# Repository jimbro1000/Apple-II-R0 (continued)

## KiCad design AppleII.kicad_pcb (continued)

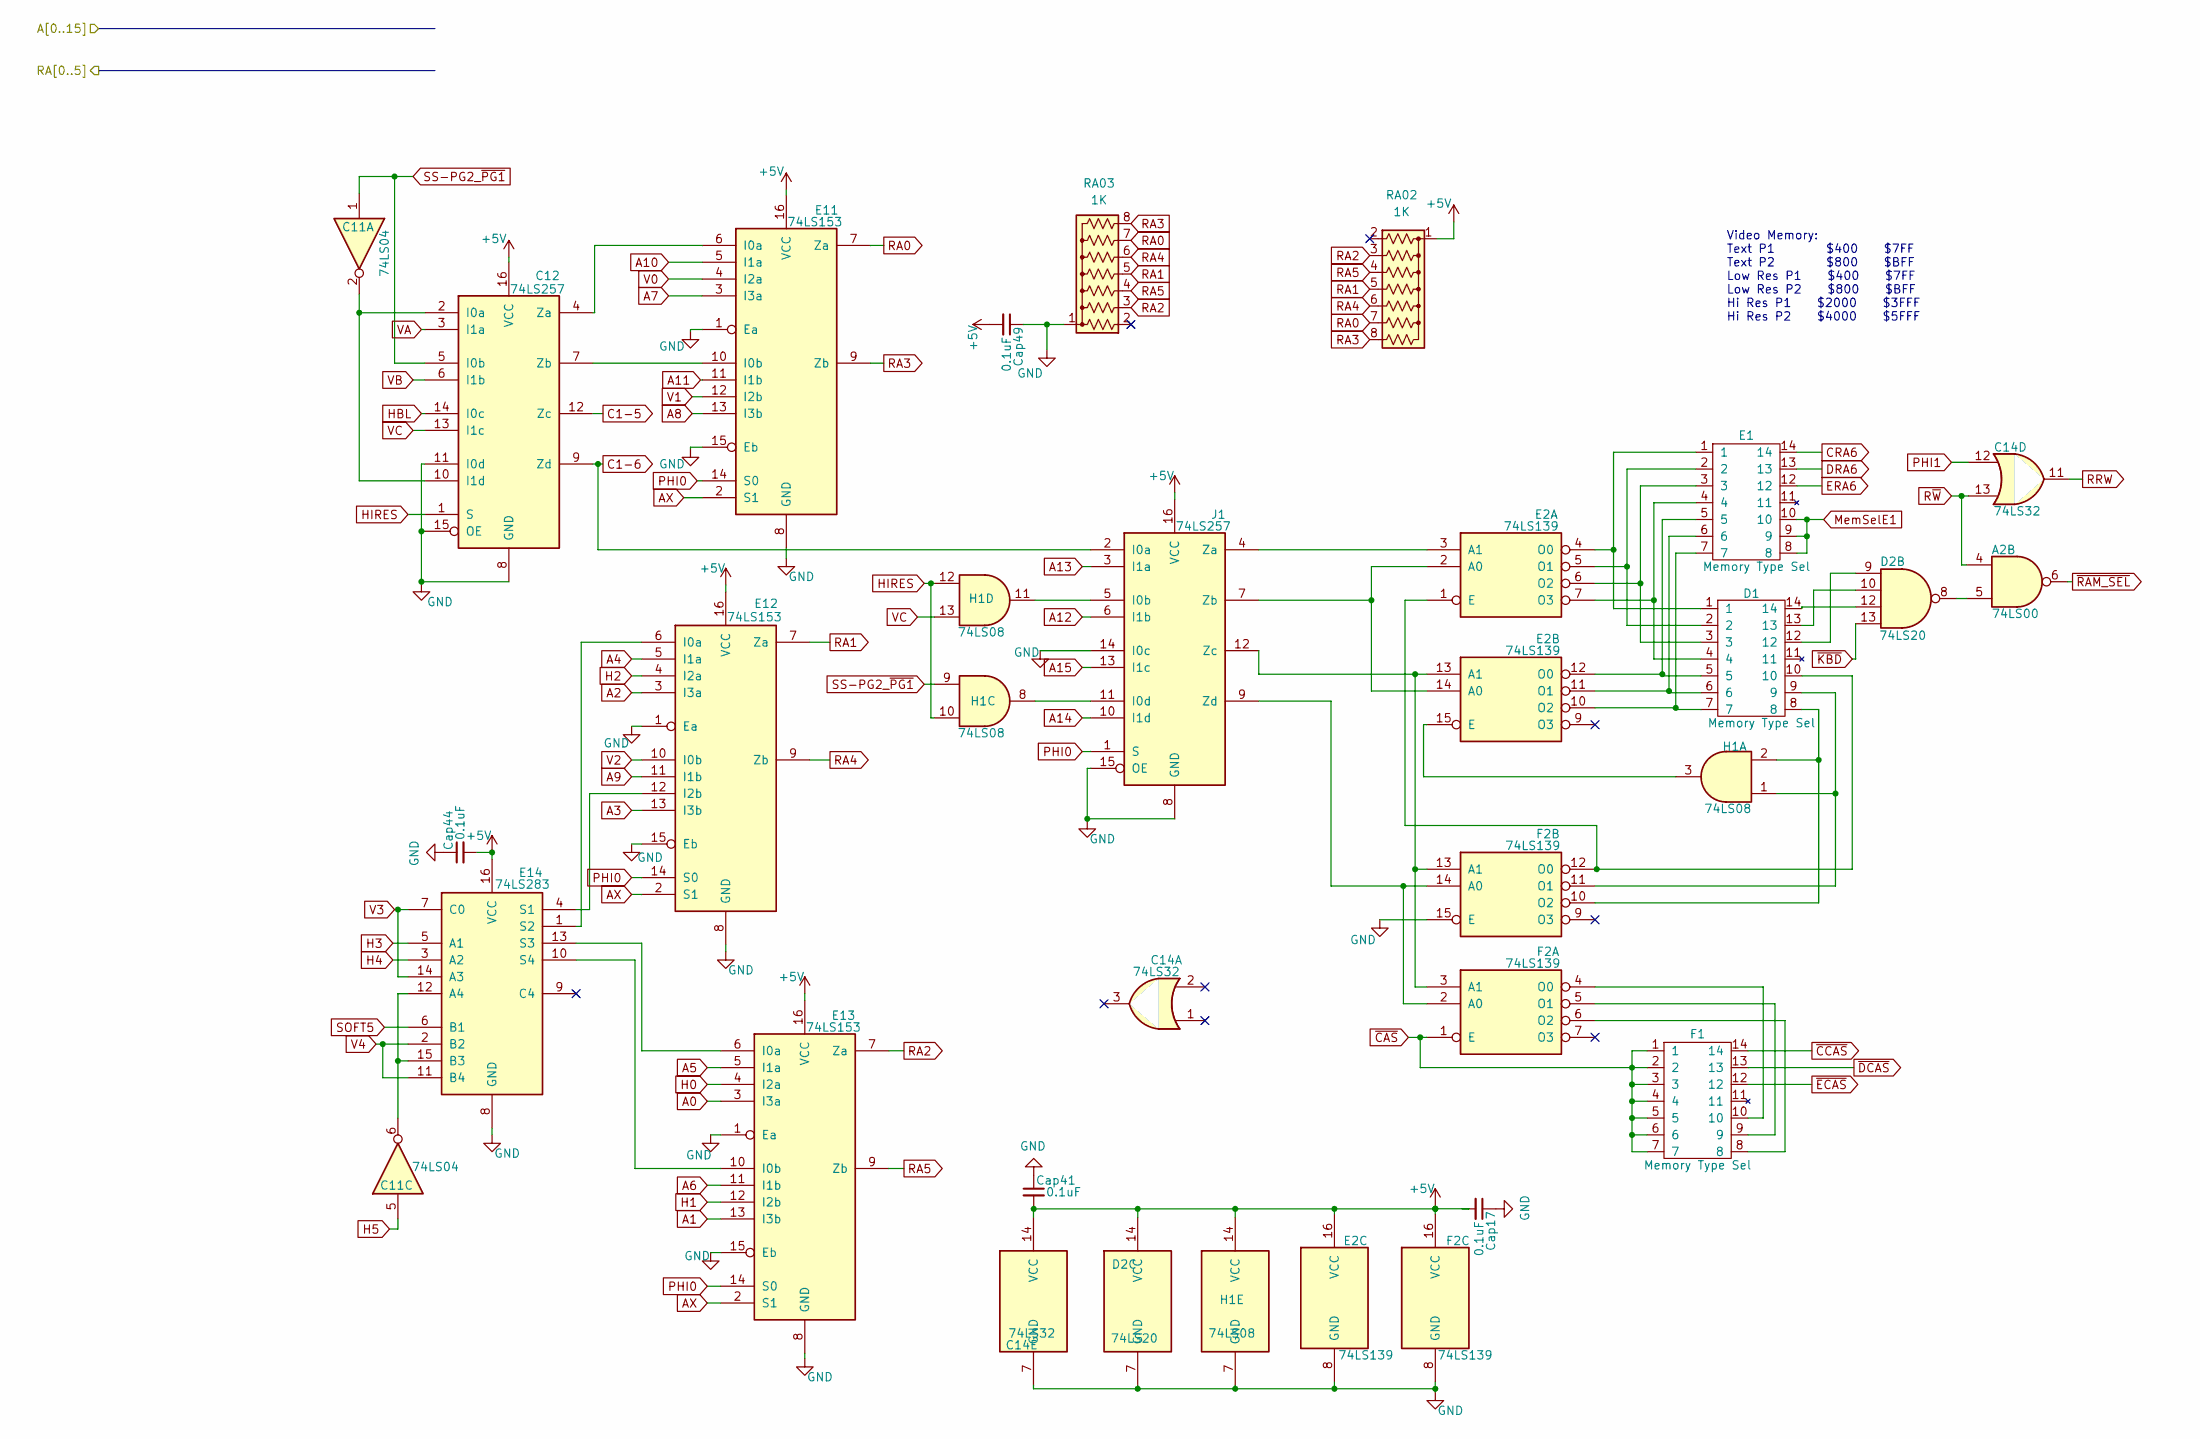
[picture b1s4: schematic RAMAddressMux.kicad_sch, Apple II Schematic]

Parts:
A2: 74LS00; DIP-14_W7.62mm
C11: 74LS04; DIP-14_W7.62mm
C12: 74LS257; DIP-16_W7.62mm
C14: 74LS32; DIP-14_W7.62mm
Cap17, Cap41, Cap44, Cap49: 0.1uF; C_Disc_D5.0mm_W2.5mm_P5.00mm
D1: Memory Type Sel; DIP-14_W7.62mm
D2: 74LS20; DIP-14_W7.62mm
E1: Memory Type Sel; DIP-14_W7.62mm
E2: 74LS139; DIP-16_W7.62mm
E11, E12, E13: 74LS153; DIP-16_W7.62mm
E14: 74LS283; DIP-16_W7.62mm
F1: Memory Type Sel; DIP-14_W7.62mm
F2: 74LS139; DIP-16_W7.62mm
H1: 74LS08; DIP-14_W7.62mm
J1: 74LS257; DIP-16_W7.62mm
RA02, RA03: 1K; R_Array_SIP8

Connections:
+5V: C12.16 (VCC), C14.14 (VCC), Cap17.2, Cap41.2, Cap44.2, Cap49.2, D2.14 (VCC), E2.16 (VCC), E11.16 (VCC), E12.16 (VCC), E13.16 (VCC), E14.16 (VCC), F2.16 (VCC), H1.14 (VCC), J1.16 (VCC), RA02.1 (common); also elsewhere on the board
/Clock Generation/H0: E13.4 (I2a); also elsewhere on the board
/Clock Generation/H1: E13.12 (I2b); also elsewhere on the board
/Clock Generation/H2: E12.4 (I2a); also elsewhere on the board
/Clock Generation/H3: E14.5 (A1); also elsewhere on the board
/Clock Generation/H4: E14.3 (A2); also elsewhere on the board
/Clock Generation/H5: C11.5; also elsewhere on the board
/Clock Generation/V1: E11.12 (I2b); also elsewhere on the board
/Clock Generation/V2: E12.10 (I0b); also elsewhere on the board
/Clock Generation/V3: E14.7 (C0), E14.14 (A3); also elsewhere on the board
/Clock Generation/V4: E14.2 (B2), E14.11 (B4); also elsewhere on the board
A0: E13.3 (I3a); also elsewhere on the board
A1: E13.13 (I3b); also elsewhere on the board
A2: E12.3 (I3a); also elsewhere on the board
A3: E12.13 (I3b); also elsewhere on the board
A4: E12.5 (I1a); also elsewhere on the board
A5: E13.5 (I1a); also elsewhere on the board
A6: E13.11 (I1b); also elsewhere on the board
A7: E11.3 (I3a); also elsewhere on the board
A8: E11.13 (I3b); also elsewhere on the board
A9: E12.11 (I1b); also elsewhere on the board
A10: E11.5 (I1a); also elsewhere on the board
A11: E11.11 (I1b); also elsewhere on the board
A12: J1.6 (I1b); also elsewhere on the board
A13: J1.3 (I1a); also elsewhere on the board
A14: J1.10 (I1d); also elsewhere on the board
A15: J1.13 (I1c); also elsewhere on the board
AX: E11.2 (S1), E12.2 (S1), E13.2 (S1); also elsewhere on the board
C1-5: C12.12 (Zc); also elsewhere on the board
C1-6: C12.9 (Zd), J1.2 (I0a); also elsewhere on the board
CRA6: E1.14; also elsewhere on the board
DRA6: E1.13; also elsewhere on the board
ERA6: E1.12; also elsewhere on the board
GND: C12.8 (GND), C12.11 (I0d), C12.15 (OE), C14.7 (GND), Cap17.1, Cap41.1, Cap44.1, Cap49.1, D2.7 (GND), E2.8 (GND), E11.1 (Ea), E11.8 (GND), E11.15 (Eb), E12.1 (Ea), E12.8 (GND), E12.15 (Eb), E13.1 (Ea), E13.8 (GND), E13.15 (Eb), E14.8 (GND), F2.8 (GND), F2.15 (E), H1.7 (GND), J1.8 (GND), J1.14 (I0c), J1.15 (OE), RA03.1 (common); also elsewhere on the board
HBL: C12.14 (I0c); also elsewhere on the board
HIRES: C12.1 (S), H1.10, H1.12; also elsewhere on the board
MemSelE1: E1.8, E1.9, E1.10; also elsewhere on the board
unnamed: A2.5, D2.8
unnamed: C11.2, C12.2 (I0a), C12.10 (I1d)
unnamed: C12.4 (Za), E11.6 (I0a)
unnamed: C12.7 (Zb), E11.10 (I0b)
unnamed: D1.12, D2.9
unnamed: D1.13, D2.10
unnamed: D1.14, D2.12
unnamed: E2.2 (A0), E2.14 (A0), J1.7 (Zb)
unnamed: E2.3 (A1), J1.4 (Za)
unnamed: D1.10, E2.1 (E), F2.12 (O0)
unnamed 186: D1.1, E1.1, E2.4 (O0); also elsewhere on the board
unnamed: D1.2, E1.2, E2.5 (O1)
unnamed: D1.3, E1.3, E2.6 (O2)
unnamed: D1.4, E1.4, E2.7 (O3)
unnamed: E2.13 (A1), F2.3 (A1), F2.13 (A1), J1.12 (Zc)
unnamed: E2.15 (E), H1.3
unnamed: D1.5, E1.5, E2.12 (O0)
unnamed: D1.6, E1.6, E2.11 (O1)
unnamed: D1.7, E1.7, E2.10 (O2)
unnamed: E12.6 (I0a), E14.1 (S2)
unnamed: E12.12 (I2b), E14.4 (S1)
unnamed: E13.6 (I0a), E14.13 (S3)
unnamed: E13.10 (I0b), E14.10 (S4)
unnamed: C11.6, E14.12 (A4), E14.15 (B3)
unnamed: F2.2 (A0), F2.14 (A0), J1.9 (Zd)
unnamed: F1.10, F2.4 (O0)
unnamed: F1.9, F2.5 (O1)
unnamed: F1.8, F2.6 (O2)
unnamed: D1.9, F2.11 (O1), H1.1
unnamed: D1.8, F2.10 (O2), H1.2
unnamed: H1.11, J1.5 (I0b)
unnamed: H1.8, J1.11 (I0d)
PHI0: E11.14 (S0), E12.14 (S0), E13.14 (S0), J1.1 (S); also elsewhere on the board
PHI1: C14.12; also elsewhere on the board
RA0: E11.7 (Za), RA02.7 (R6), RA03.7 (R6); also elsewhere on the board
RA1: E12.7 (Za), RA02.5 (R4), RA03.5 (R4); also elsewhere on the board
RA2: E13.7 (Za), RA02.3 (R2), RA03.3 (R2); also elsewhere on the board
RA3: E11.9 (Zb), RA02.8 (R7), RA03.8 (R7); also elsewhere on the board
RA4: E12.9 (Zb), RA02.6 (R5), RA03.6 (R5); also elsewhere on the board
RA5: E13.9 (Zb), RA02.4 (R3), RA03.4 (R3); also elsewhere on the board
RRW: C14.11; also elsewhere on the board
R~W: A2.4, C14.13; also elsewhere on the board
SOFT5: E14.6 (B1); also elsewhere on the board
SS-PG2_~PG1: C11.1, C12.5 (I0b), H1.9; also elsewhere on the board
V0: E11.4 (I2a); also elsewhere on the board
VA: C12.3 (I1a); also elsewhere on the board
VB: C12.6 (I1b); also elsewhere on the board
VC: C12.13 (I1c), H1.13; also elsewhere on the board
~CAS: F1.1, F1.2, F1.3, F1.4, F1.5, F1.6, F1.7, F2.1 (E); also elsewhere on the board
~CCAS: F1.14; also elsewhere on the board
~DCAS: F1.13; also elsewhere on the board
~ECAS: F1.12; also elsewhere on the board
~KBD: D2.13; also elsewhere on the board
~RAM_SEL: A2.6; also elsewhere on the board

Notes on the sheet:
Video Memory: Text P1 $400 $7FF Text P2 $800 $BFF Low Res P1 $400 $7FF Low Res P2 $800 $BFF Hi Res P1 $2000 $3FFF Hi Res P2 $4000 $5FFF

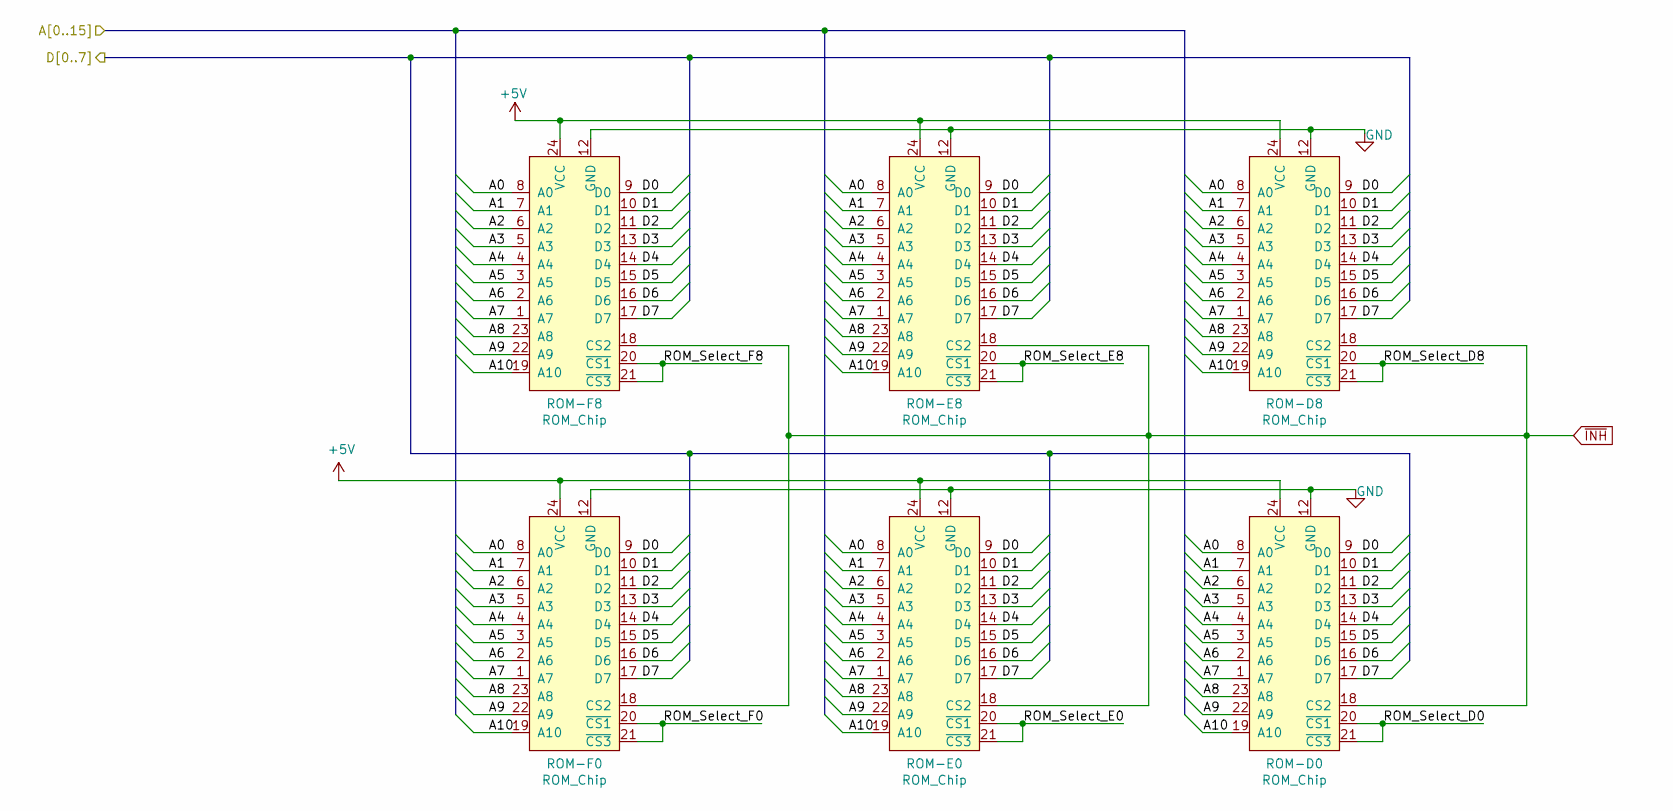
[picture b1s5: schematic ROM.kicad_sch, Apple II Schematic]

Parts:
ROM-D0, ROM-D8: ROM_Chip; DIP-24_W15.24mm
ROM-E0, ROM-E8: ROM_Chip; DIP-24_W15.24mm
ROM-F0, ROM-F8: ROM_Chip; DIP-24_W15.24mm

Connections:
+5V: ROM-D0.24 (VCC), ROM-D8.24 (VCC), ROM-E0.24 (VCC), ROM-E8.24 (VCC), ROM-F0.24 (VCC), ROM-F8.24 (VCC); also elsewhere on the board
A0: ROM-D0.8 (A0), ROM-D8.8 (A0), ROM-E0.8 (A0), ROM-E8.8 (A0), ROM-F0.8 (A0), ROM-F8.8 (A0); also elsewhere on the board
A1: ROM-D0.7 (A1), ROM-D8.7 (A1), ROM-E0.7 (A1), ROM-E8.7 (A1), ROM-F0.7 (A1), ROM-F8.7 (A1); also elsewhere on the board
A2: ROM-D0.6 (A2), ROM-D8.6 (A2), ROM-E0.6 (A2), ROM-E8.6 (A2), ROM-F0.6 (A2), ROM-F8.6 (A2); also elsewhere on the board
A3: ROM-D0.5 (A3), ROM-D8.5 (A3), ROM-E0.5 (A3), ROM-E8.5 (A3), ROM-F0.5 (A3), ROM-F8.5 (A3); also elsewhere on the board
A4: ROM-D0.4 (A4), ROM-D8.4 (A4), ROM-E0.4 (A4), ROM-E8.4 (A4), ROM-F0.4 (A4), ROM-F8.4 (A4); also elsewhere on the board
A5: ROM-D0.3 (A5), ROM-D8.3 (A5), ROM-E0.3 (A5), ROM-E8.3 (A5), ROM-F0.3 (A5), ROM-F8.3 (A5); also elsewhere on the board
A6: ROM-D0.2 (A6), ROM-D8.2 (A6), ROM-E0.2 (A6), ROM-E8.2 (A6), ROM-F0.2 (A6), ROM-F8.2 (A6); also elsewhere on the board
A7: ROM-D0.1 (A7), ROM-D8.1 (A7), ROM-E0.1 (A7), ROM-E8.1 (A7), ROM-F0.1 (A7), ROM-F8.1 (A7); also elsewhere on the board
A8: ROM-D0.23 (A8), ROM-D8.23 (A8), ROM-E0.23 (A8), ROM-E8.23 (A8), ROM-F0.23 (A8), ROM-F8.23 (A8); also elsewhere on the board
A9: ROM-D0.22 (A9), ROM-D8.22 (A9), ROM-E0.22 (A9), ROM-E8.22 (A9), ROM-F0.22 (A9), ROM-F8.22 (A9); also elsewhere on the board
A10: ROM-D0.19 (A10), ROM-D8.19 (A10), ROM-E0.19 (A10), ROM-E8.19 (A10), ROM-F0.19 (A10), ROM-F8.19 (A10); also elsewhere on the board
D0: ROM-D0.9 (D0), ROM-D8.9 (D0), ROM-E0.9 (D0), ROM-E8.9 (D0), ROM-F0.9 (D0), ROM-F8.9 (D0); also elsewhere on the board
D1: ROM-D0.10 (D1), ROM-D8.10 (D1), ROM-E0.10 (D1), ROM-E8.10 (D1), ROM-F0.10 (D1), ROM-F8.10 (D1); also elsewhere on the board
D2: ROM-D0.11 (D2), ROM-D8.11 (D2), ROM-E0.11 (D2), ROM-E8.11 (D2), ROM-F0.11 (D2), ROM-F8.11 (D2); also elsewhere on the board
D3: ROM-D0.13 (D3), ROM-D8.13 (D3), ROM-E0.13 (D3), ROM-E8.13 (D3), ROM-F0.13 (D3), ROM-F8.13 (D3); also elsewhere on the board
D4: ROM-D0.14 (D4), ROM-D8.14 (D4), ROM-E0.14 (D4), ROM-E8.14 (D4), ROM-F0.14 (D4), ROM-F8.14 (D4); also elsewhere on the board
D5: ROM-D0.15 (D5), ROM-D8.15 (D5), ROM-E0.15 (D5), ROM-E8.15 (D5), ROM-F0.15 (D5), ROM-F8.15 (D5); also elsewhere on the board
D6: ROM-D0.16 (D6), ROM-D8.16 (D6), ROM-E0.16 (D6), ROM-E8.16 (D6), ROM-F0.16 (D6), ROM-F8.16 (D6); also elsewhere on the board
D7: ROM-D0.17 (D7), ROM-D8.17 (D7), ROM-E0.17 (D7), ROM-E8.17 (D7), ROM-F0.17 (D7), ROM-F8.17 (D7); also elsewhere on the board
GND: ROM-D0.12 (GND), ROM-D8.12 (GND), ROM-E0.12 (GND), ROM-E8.12 (GND), ROM-F0.12 (GND), ROM-F8.12 (GND); also elsewhere on the board
ROM_SELECT_D0: ROM-D0.20 (~CS1), ROM-D0.21 (~CS3); also elsewhere on the board
ROM_SELECT_D8: ROM-D8.20 (~CS1), ROM-D8.21 (~CS3); also elsewhere on the board
ROM_SELECT_E0: ROM-E0.20 (~CS1), ROM-E0.21 (~CS3); also elsewhere on the board
ROM_SELECT_E8: ROM-E8.20 (~CS1), ROM-E8.21 (~CS3); also elsewhere on the board
ROM_SELECT_F0: ROM-F0.20 (~CS1), ROM-F0.21 (~CS3); also elsewhere on the board
ROM_SELECT_F8: ROM-F8.20 (~CS1), ROM-F8.21 (~CS3); also elsewhere on the board
~INH: ROM-D0.18 (CS2), ROM-D8.18 (CS2), ROM-E0.18 (CS2), ROM-E8.18 (CS2), ROM-F0.18 (CS2), ROM-F8.18 (CS2); also elsewhere on the board

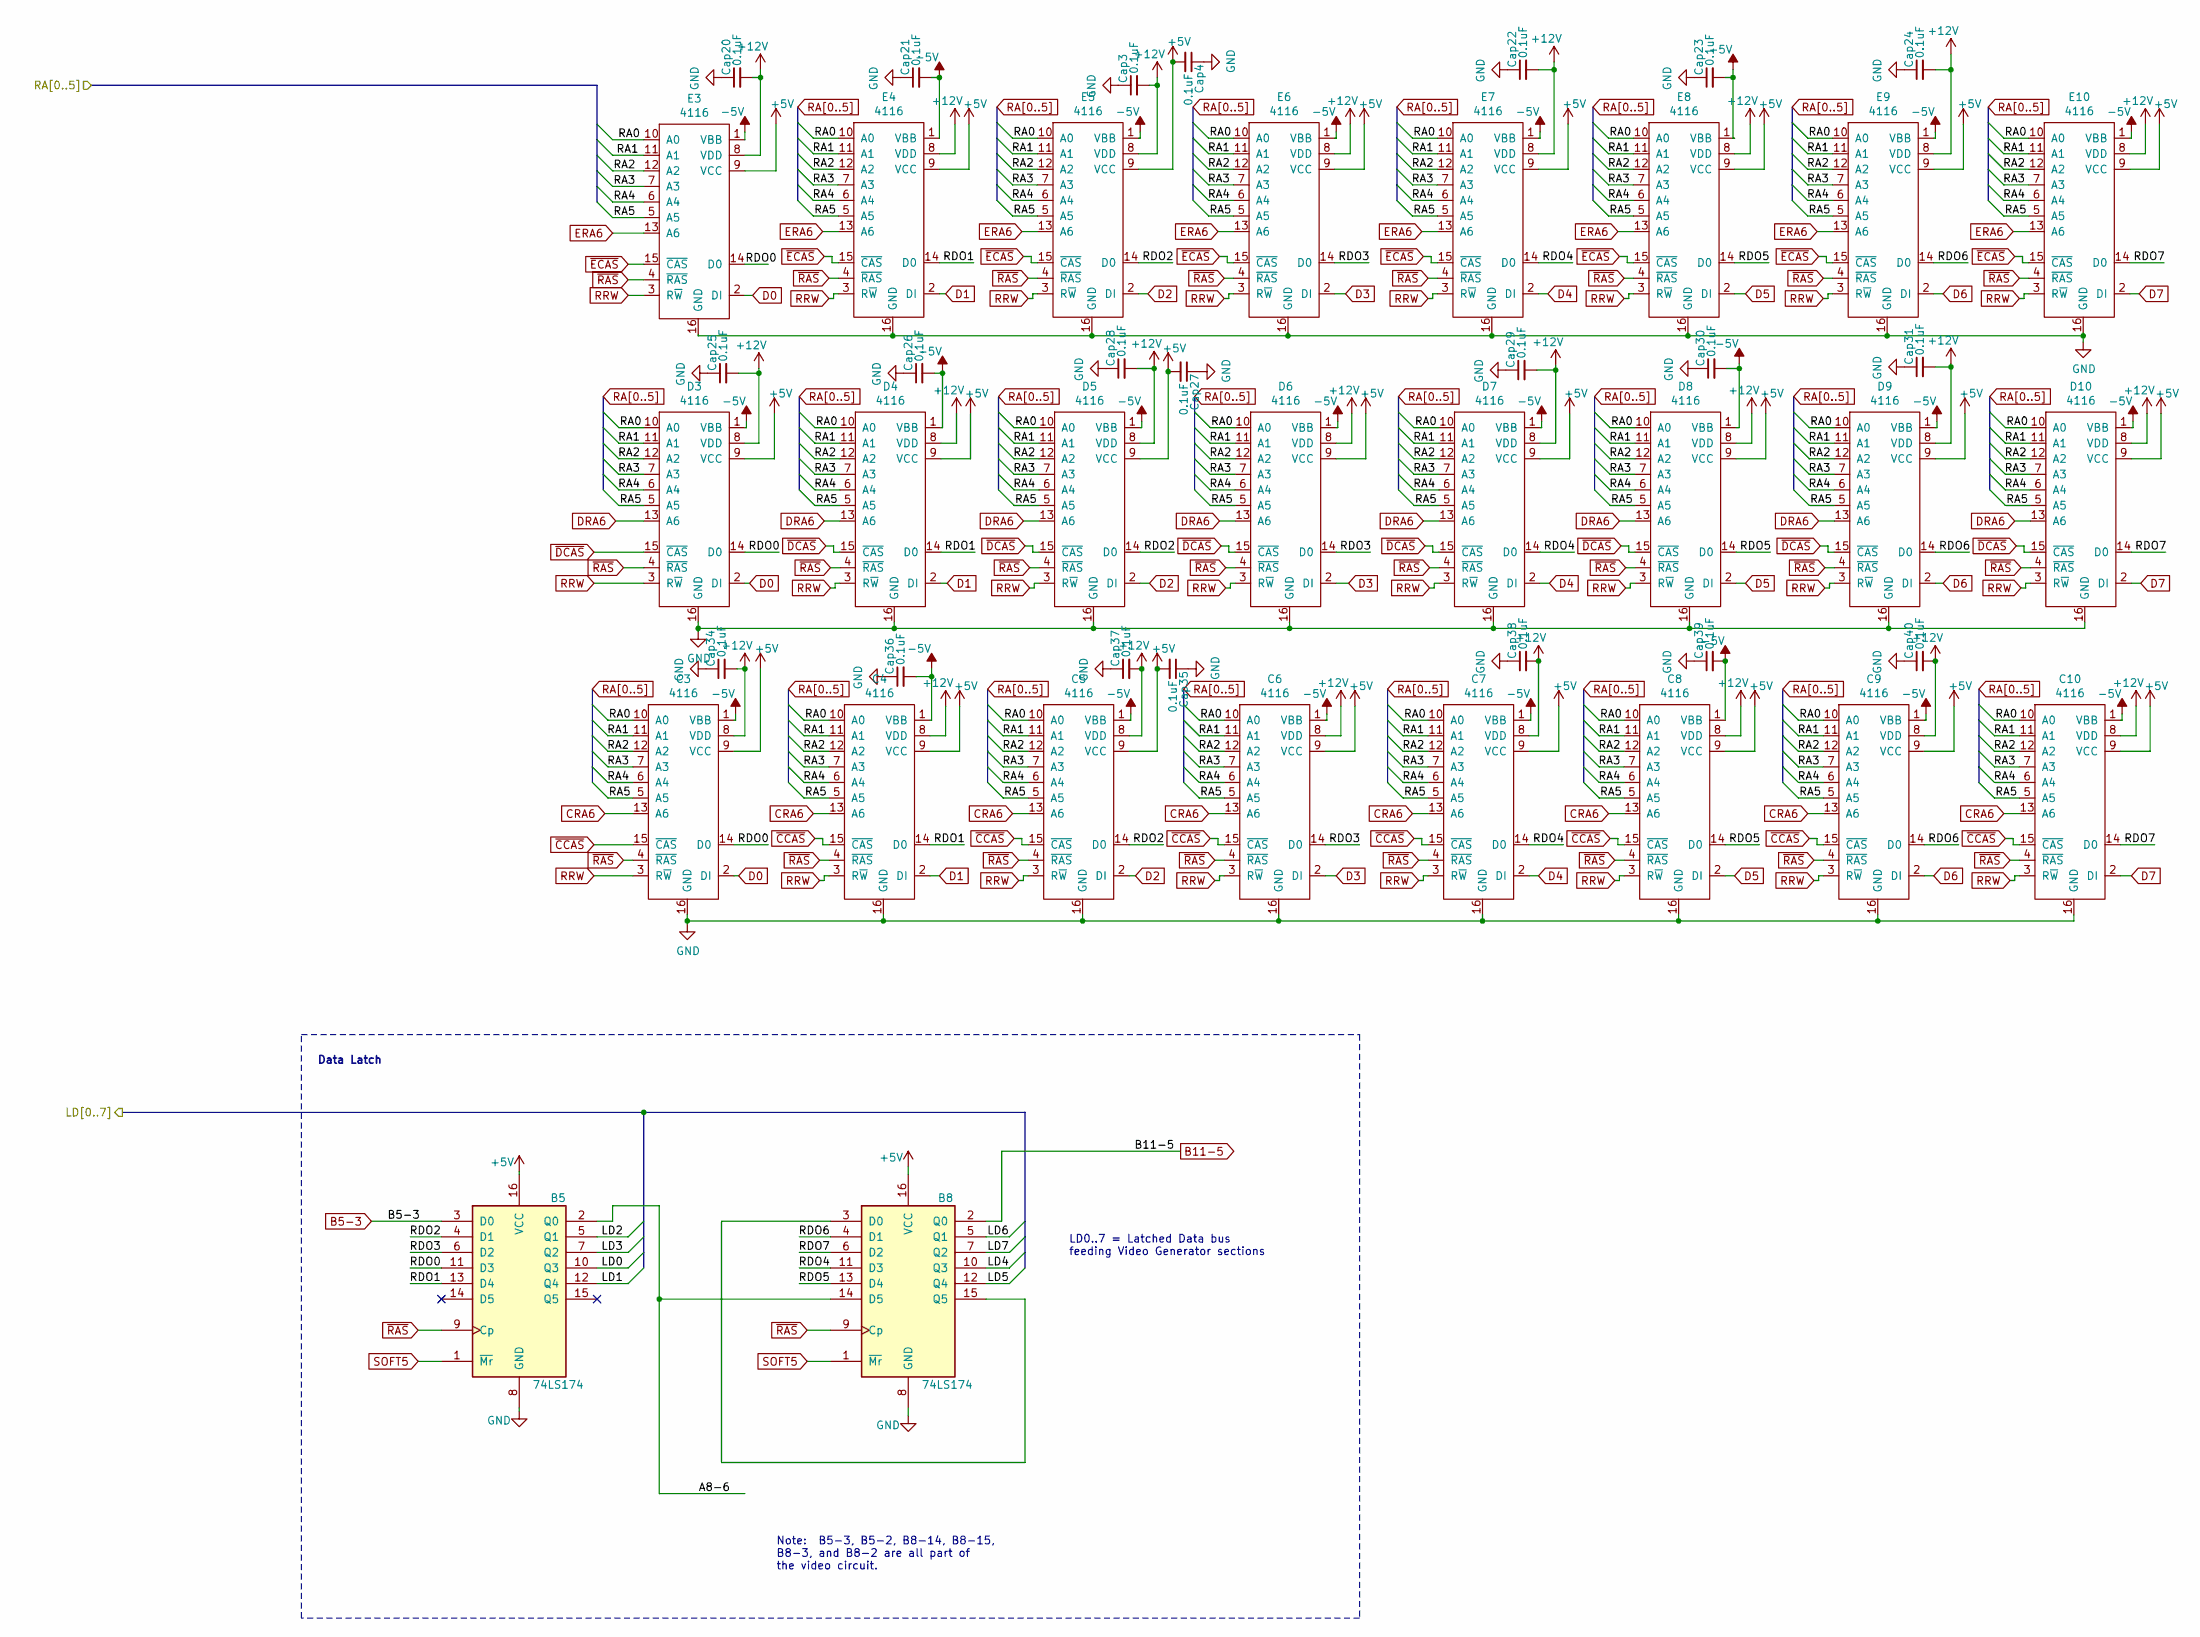
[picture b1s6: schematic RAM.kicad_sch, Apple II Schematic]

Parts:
B5, B8: 74LS174; DIP-16_W7.62mm
C3, C4, C5, C6, C7, C8, C9, C10: 4116; DIP-16_W7.62mm
Cap3, Cap4, Cap20, Cap21, Cap22, Cap23, Cap24, Cap25, Cap26, Cap27, Cap28, Cap29, Cap30, Cap31, Cap34, Cap35, Cap36, Cap37, Cap38, Cap39, Cap40: 0.1uF; C_Disc_D5.0mm_W2.5mm_P5.00mm
D3, D4, D5, D6, D7, D8, D9, D10: 4116; DIP-16_W7.62mm
E3, E4, E5, E6, E7, E8, E9, E10: 4116; DIP-16_W7.62mm

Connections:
+5V: B5.16 (VCC), B8.16 (VCC), C3.9 (VCC), C4.9 (VCC), C5.9 (VCC), C6.9 (VCC), C7.9 (VCC), C8.9 (VCC), C9.9 (VCC), C10.9 (VCC), Cap4.2, Cap27.2, Cap35.2, D3.9 (VCC), D4.9 (VCC), D5.9 (VCC), D6.9 (VCC), D7.9 (VCC), D8.9 (VCC), D9.9 (VCC), D10.9 (VCC), E3.9 (VCC), E4.9 (VCC), E5.9 (VCC), E6.9 (VCC), E7.9 (VCC), E8.9 (VCC), E9.9 (VCC), E10.9 (VCC); also elsewhere on the board
+12V: C3.8 (VDD), C4.8 (VDD), C5.8 (VDD), C6.8 (VDD), C7.8 (VDD), C8.8 (VDD), C9.8 (VDD), C10.8 (VDD), Cap3.2, Cap20.2, Cap22.2, Cap24.2, Cap25.2, Cap28.2, Cap29.2, Cap31.2, Cap34.2, Cap37.2, Cap38.2, Cap40.2, D3.8 (VDD), D4.8 (VDD), D5.8 (VDD), D6.8 (VDD), D7.8 (VDD), D8.8 (VDD), D9.8 (VDD), D10.8 (VDD), E3.8 (VDD), E4.8 (VDD), E5.8 (VDD), E6.8 (VDD), E7.8 (VDD), E8.8 (VDD), E9.8 (VDD), E10.8 (VDD); also elsewhere on the board
-5V: C3.1 (VBB), C4.1 (VBB), C5.1 (VBB), C6.1 (VBB), C7.1 (VBB), C8.1 (VBB), C9.1 (VBB), C10.1 (VBB), Cap21.2, Cap23.2, Cap26.2, Cap30.2, Cap36.2, Cap39.2, D3.1 (VBB), D4.1 (VBB), D5.1 (VBB), D6.1 (VBB), D7.1 (VBB), D8.1 (VBB), D9.1 (VBB), D10.1 (VBB), E3.1 (VBB), E4.1 (VBB), E5.1 (VBB), E6.1 (VBB), E7.1 (VBB), E8.1 (VBB), E9.1 (VBB), E10.1 (VBB); also elsewhere on the board
/CPU Tranceiver Driver and Data MUX/LD0: B5.10 (Q3); also elsewhere on the board
/CPU Tranceiver Driver and Data MUX/LD1: B5.12 (Q4); also elsewhere on the board
/CPU Tranceiver Driver and Data MUX/LD2: B5.5 (Q1); also elsewhere on the board
/CPU Tranceiver Driver and Data MUX/LD3: B5.7 (Q2); also elsewhere on the board
/CPU Tranceiver Driver and Data MUX/LD4: B8.10 (Q3); also elsewhere on the board
/CPU Tranceiver Driver and Data MUX/LD5: B8.12 (Q4); also elsewhere on the board
/CPU Tranceiver Driver and Data MUX/LD6: B8.5 (Q1); also elsewhere on the board
/CPU Tranceiver Driver and Data MUX/LD7: B8.7 (Q2); also elsewhere on the board
/RAM and Data Latch/A8-6: B5.2 (Q0), B8.14 (D5)
/RAM and Data Latch/RDO0: B5.11 (D3), C3.14 (D0), D3.14 (D0), E3.14 (D0)
/RAM and Data Latch/RDO1: B5.13 (D4), C4.14 (D0), D4.14 (D0), E4.14 (D0)
/RAM and Data Latch/RDO2: B5.4 (D1), C5.14 (D0), D5.14 (D0), E5.14 (D0)
/RAM and Data Latch/RDO3: B5.6 (D2), C6.14 (D0), D6.14 (D0), E6.14 (D0)
/RAM and Data Latch/RDO4: B8.11 (D3), C7.14 (D0), D7.14 (D0), E7.14 (D0)
/RAM and Data Latch/RDO5: B8.13 (D4), C8.14 (D0), D8.14 (D0), E8.14 (D0)
/RAM and Data Latch/RDO6: B8.4 (D1), C9.14 (D0), D9.14 (D0), E9.14 (D0)
/RAM and Data Latch/RDO7: B8.6 (D2), C10.14 (D0), D10.14 (D0), E10.14 (D0)
B5-3: B5.3 (D0); also elsewhere on the board
B11-5: B8.2 (Q0); also elsewhere on the board
CRA6: C3.13 (A6), C4.13 (A6), C5.13 (A6), C6.13 (A6), C7.13 (A6), C8.13 (A6), C9.13 (A6), C10.13 (A6); also elsewhere on the board
D0: C3.2 (DI), D3.2 (DI), E3.2 (DI); also elsewhere on the board
D1: C4.2 (DI), D4.2 (DI), E4.2 (DI); also elsewhere on the board
D2: C5.2 (DI), D5.2 (DI), E5.2 (DI); also elsewhere on the board
D3: C6.2 (DI), D6.2 (DI), E6.2 (DI); also elsewhere on the board
D4: C7.2 (DI), D7.2 (DI), E7.2 (DI); also elsewhere on the board
D5: C8.2 (DI), D8.2 (DI), E8.2 (DI); also elsewhere on the board
D6: C9.2 (DI), D9.2 (DI), E9.2 (DI); also elsewhere on the board
D7: C10.2 (DI), D10.2 (DI), E10.2 (DI); also elsewhere on the board
DRA6: D3.13 (A6), D4.13 (A6), D5.13 (A6), D6.13 (A6), D7.13 (A6), D8.13 (A6), D9.13 (A6), D10.13 (A6); also elsewhere on the board
ERA6: E3.13 (A6), E4.13 (A6), E5.13 (A6), E6.13 (A6), E7.13 (A6), E8.13 (A6), E9.13 (A6), E10.13 (A6); also elsewhere on the board
GND: B5.8 (GND), B8.8 (GND), C3.16 (GND), C4.16 (GND), C5.16 (GND), C6.16 (GND), C7.16 (GND), C8.16 (GND), C9.16 (GND), C10.16 (GND), Cap3.1, Cap4.1, Cap20.1, Cap21.1, Cap22.1, Cap23.1, Cap24.1, Cap25.1, Cap26.1, Cap27.1, Cap28.1, Cap29.1, Cap30.1, Cap31.1, Cap34.1, Cap35.1, Cap36.1, Cap37.1, Cap38.1, Cap39.1, Cap40.1, D3.16 (GND), D4.16 (GND), D5.16 (GND), D6.16 (GND), D7.16 (GND), D8.16 (GND), D9.16 (GND), D10.16 (GND), E3.16 (GND), E4.16 (GND), E5.16 (GND), E6.16 (GND), E7.16 (GND), E8.16 (GND), E9.16 (GND), E10.16 (GND); also elsewhere on the board
unnamed: B8.3 (D0), B8.15 (Q5)
RA0: C3.10 (A0), C4.10 (A0), C5.10 (A0), C6.10 (A0), C7.10 (A0), C8.10 (A0), C9.10 (A0), C10.10 (A0), D3.10 (A0), D4.10 (A0), D5.10 (A0), D6.10 (A0), D7.10 (A0), D8.10 (A0), D9.10 (A0), D10.10 (A0), E3.10 (A0), E4.10 (A0), E5.10 (A0), E6.10 (A0), E7.10 (A0), E8.10 (A0), E9.10 (A0), E10.10 (A0); also elsewhere on the board
RA1: C3.11 (A1), C4.11 (A1), C5.11 (A1), C6.11 (A1), C7.11 (A1), C8.11 (A1), C9.11 (A1), C10.11 (A1), D3.11 (A1), D4.11 (A1), D5.11 (A1), D6.11 (A1), D7.11 (A1), D8.11 (A1), D9.11 (A1), D10.11 (A1), E3.11 (A1), E4.11 (A1), E5.11 (A1), E6.11 (A1), E7.11 (A1), E8.11 (A1), E9.11 (A1), E10.11 (A1); also elsewhere on the board
RA2: C3.12 (A2), C4.12 (A2), C5.12 (A2), C6.12 (A2), C7.12 (A2), C8.12 (A2), C9.12 (A2), C10.12 (A2), D3.12 (A2), D4.12 (A2), D5.12 (A2), D6.12 (A2), D7.12 (A2), D8.12 (A2), D9.12 (A2), D10.12 (A2), E3.12 (A2), E4.12 (A2), E5.12 (A2), E6.12 (A2), E7.12 (A2), E8.12 (A2), E9.12 (A2), E10.12 (A2); also elsewhere on the board
RA3: C3.7 (A3), C4.7 (A3), C5.7 (A3), C6.7 (A3), C7.7 (A3), C8.7 (A3), C9.7 (A3), C10.7 (A3), D3.7 (A3), D4.7 (A3), D5.7 (A3), D6.7 (A3), D7.7 (A3), D8.7 (A3), D9.7 (A3), D10.7 (A3), E3.7 (A3), E4.7 (A3), E5.7 (A3), E6.7 (A3), E7.7 (A3), E8.7 (A3), E9.7 (A3), E10.7 (A3); also elsewhere on the board
RA4: C3.6 (A4), C4.6 (A4), C5.6 (A4), C6.6 (A4), C7.6 (A4), C8.6 (A4), C9.6 (A4), C10.6 (A4), D3.6 (A4), D4.6 (A4), D5.6 (A4), D6.6 (A4), D7.6 (A4), D8.6 (A4), D9.6 (A4), D10.6 (A4), E3.6 (A4), E4.6 (A4), E5.6 (A4), E6.6 (A4), E7.6 (A4), E8.6 (A4), E9.6 (A4), E10.6 (A4); also elsewhere on the board
RA5: C3.5 (A5), C4.5 (A5), C5.5 (A5), C6.5 (A5), C7.5 (A5), C8.5 (A5), C9.5 (A5), C10.5 (A5), D3.5 (A5), D4.5 (A5), D5.5 (A5), D6.5 (A5), D7.5 (A5), D8.5 (A5), D9.5 (A5), D10.5 (A5), E3.5 (A5), E4.5 (A5), E5.5 (A5), E6.5 (A5), E7.5 (A5), E8.5 (A5), E9.5 (A5), E10.5 (A5); also elsewhere on the board
RRW: C3.3 (R~W), C4.3 (R~W), C5.3 (R~W), C6.3 (R~W), C7.3 (R~W), C8.3 (R~W), C9.3 (R~W), C10.3 (R~W), D3.3 (R~W), D4.3 (R~W), D5.3 (R~W), D6.3 (R~W), D7.3 (R~W), D8.3 (R~W), D9.3 (R~W), D10.3 (R~W), E3.3 (R~W), E4.3 (R~W), E5.3 (R~W), E6.3 (R~W), E7.3 (R~W), E8.3 (R~W), E9.3 (R~W), E10.3 (R~W); also elsewhere on the board
SOFT5: B5.1 (~Mr), B8.1 (~Mr); also elsewhere on the board
~CCAS: C3.15 (~CAS), C4.15 (~CAS), C5.15 (~CAS), C6.15 (~CAS), C7.15 (~CAS), C8.15 (~CAS), C9.15 (~CAS), C10.15 (~CAS); also elsewhere on the board
~DCAS: D3.15 (~CAS), D4.15 (~CAS), D5.15 (~CAS), D6.15 (~CAS), D7.15 (~CAS), D8.15 (~CAS), D9.15 (~CAS), D10.15 (~CAS); also elsewhere on the board
~ECAS: E3.15 (~CAS), E4.15 (~CAS), E5.15 (~CAS), E6.15 (~CAS), E7.15 (~CAS), E8.15 (~CAS), E9.15 (~CAS), E10.15 (~CAS); also elsewhere on the board
~RAS: B5.9 (Cp), B8.9 (Cp), C3.4 (~RAS), C4.4 (~RAS), C5.4 (~RAS), C6.4 (~RAS), C7.4 (~RAS), C8.4 (~RAS), C9.4 (~RAS), C10.4 (~RAS), D3.4 (~RAS), D4.4 (~RAS), D5.4 (~RAS), D6.4 (~RAS), D7.4 (~RAS), D8.4 (~RAS), D9.4 (~RAS), D10.4 (~RAS), E3.4 (~RAS), E4.4 (~RAS), E5.4 (~RAS), E6.4 (~RAS), E7.4 (~RAS), E8.4 (~RAS), E9.4 (~RAS), E10.4 (~RAS); also elsewhere on the board

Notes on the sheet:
LD0..7 = Latched Data bus feeding Video Generator sections
Data Latch
Note: B5-3, B5-2, B8-14, B8-15, B8-3, and B8-2 are all part of the video circuit.
